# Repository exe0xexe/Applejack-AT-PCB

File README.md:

# PCB for converting AT layout keyboards to MX
### Powered by QMK/VIAL
## Layout

## Bill Of Materials 

### To build the keyboard, you will need the following materials
- 1x STM32F401CCU6 Blackpill
- Pins and sockets for the microcontrollers (blackpill needs 20 pin stripes)
- 98 1N4148 DO-35 diodes
- 22 Wire jumpers (you can use diode legs) 
- 4 82ohm resistors (optional)
- LED (optional)

## Completed build

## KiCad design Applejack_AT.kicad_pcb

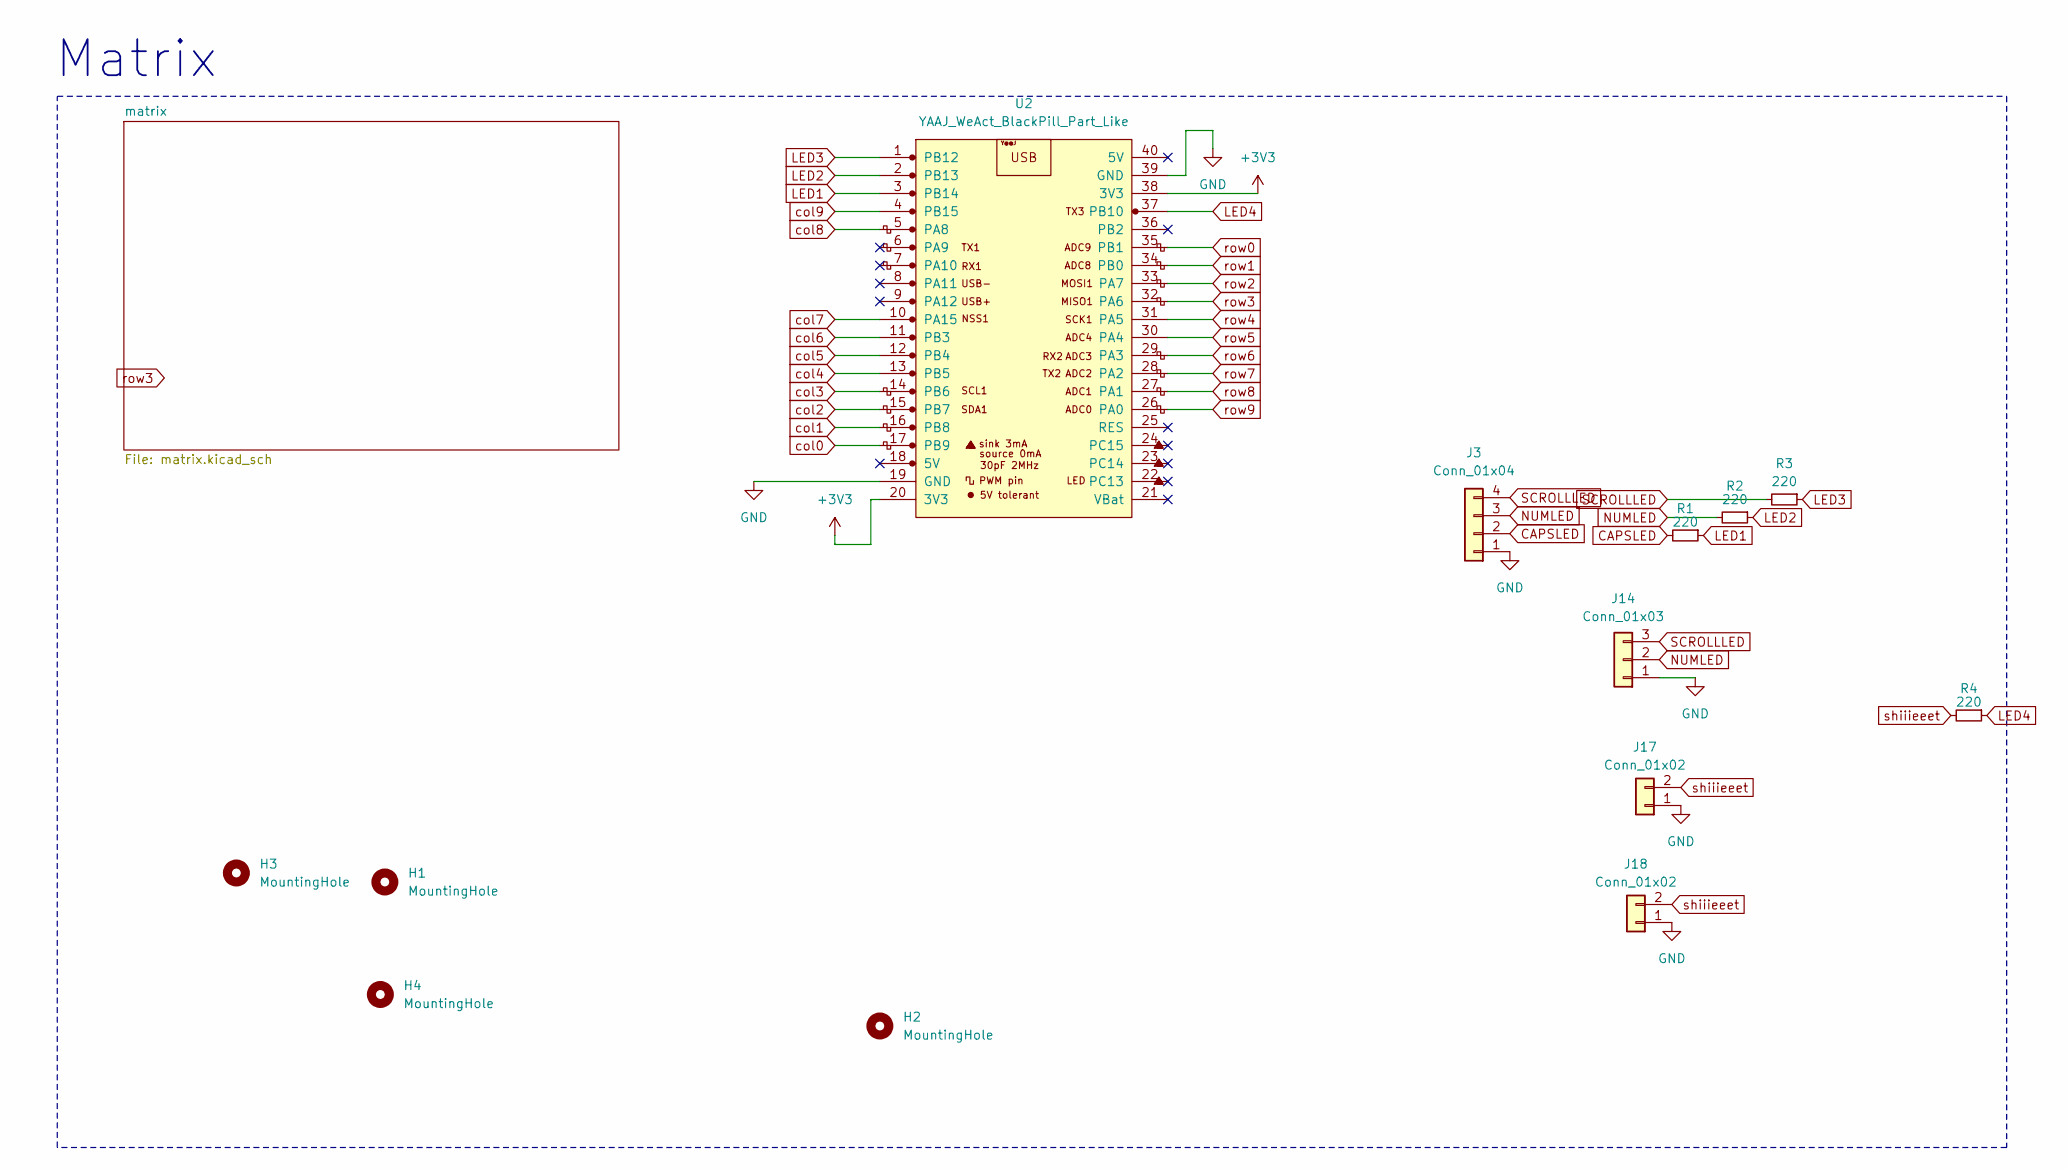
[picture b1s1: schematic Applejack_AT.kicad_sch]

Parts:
H1, H2, H3, H4: MountingHole; mousebites_2.5mm_4p
J3: Conn_01x04; PinHeader_1x04_P2.54mm_Horizontal
J14: Conn_01x03; 3pin
J17, J18: Conn_01x02; 2pin-GND
R1, R2, R3, R4: 220; R_Axial_DIN0207_L6.3mm_D2.5mm_P7.62mm_Horizontal_no_silkscr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
U2: YAAJ_WeAct_BlackPill_Part_Like; YAAJ_WeAct_BlackPill_2_twilight_sparkle_no_cut

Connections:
+3V3: U2.20 (3V3), U2.38 (3V3)
CAPSLED: J3.2, R1.2; also elsewhere on the board
GND: J3.1, J14.1, J17.1, J18.1, U2.19 (GND), U2.39 (GND); also elsewhere on the board
LED1: R1.1, U2.3 (PB14)
LED2: R2.1, U2.2 (PB13)
LED3: R3.1, U2.1 (PB12)
LED4: R4.1, U2.37 (PB10)
NUMLED: J3.3, J14.2, R2.2; also elsewhere on the board
SCROLLLED: J3.4, J14.3, R3.2; also elsewhere on the board
col0: U2.17 (PB9); also elsewhere on the board
col1: U2.16 (PB8); also elsewhere on the board
col2: U2.15 (PB7); also elsewhere on the board
col3: U2.14 (PB6); also elsewhere on the board
col4: U2.13 (PB5); also elsewhere on the board
col5: U2.12 (PB4); also elsewhere on the board
col6: U2.11 (PB3); also elsewhere on the board
col7: U2.10 (PA15); also elsewhere on the board
col8: U2.5 (PA8); also elsewhere on the board
col9: U2.4 (PB15); also elsewhere on the board
row0: U2.35 (PB1); also elsewhere on the board
row1: U2.34 (PB0); also elsewhere on the board
row2: U2.33 (PA7); also elsewhere on the board
row3: U2.32 (PA6); also elsewhere on the board
row4: U2.31 (PA5); also elsewhere on the board
row5: U2.30 (PA4); also elsewhere on the board
row6: U2.29 (PA3); also elsewhere on the board
row7: U2.28 (PA2); also elsewhere on the board
row8: U2.27 (PA1); also elsewhere on the board
row9: U2.26 (PA0); also elsewhere on the board
shiiieeet: J17.2, J18.2, R4.2; also elsewhere on the board

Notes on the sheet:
Matrix

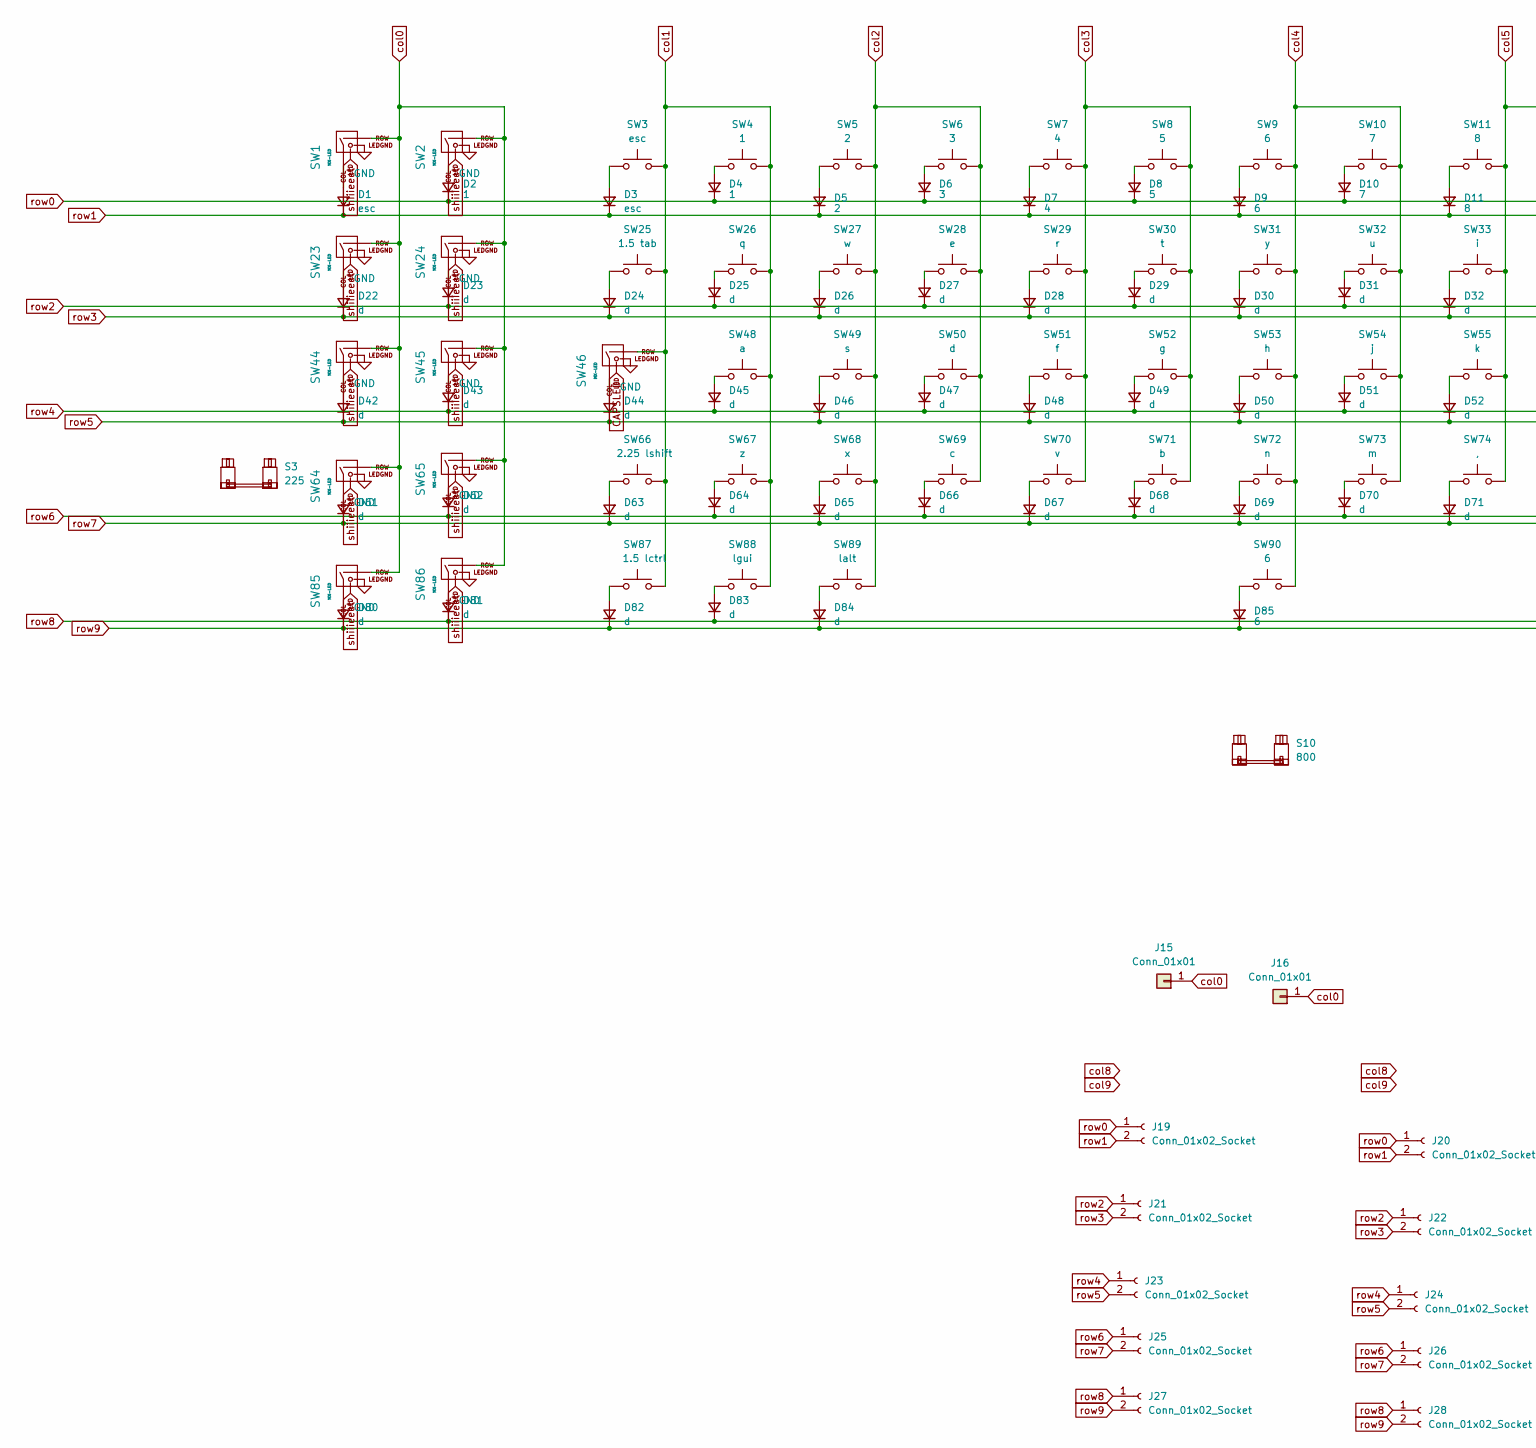
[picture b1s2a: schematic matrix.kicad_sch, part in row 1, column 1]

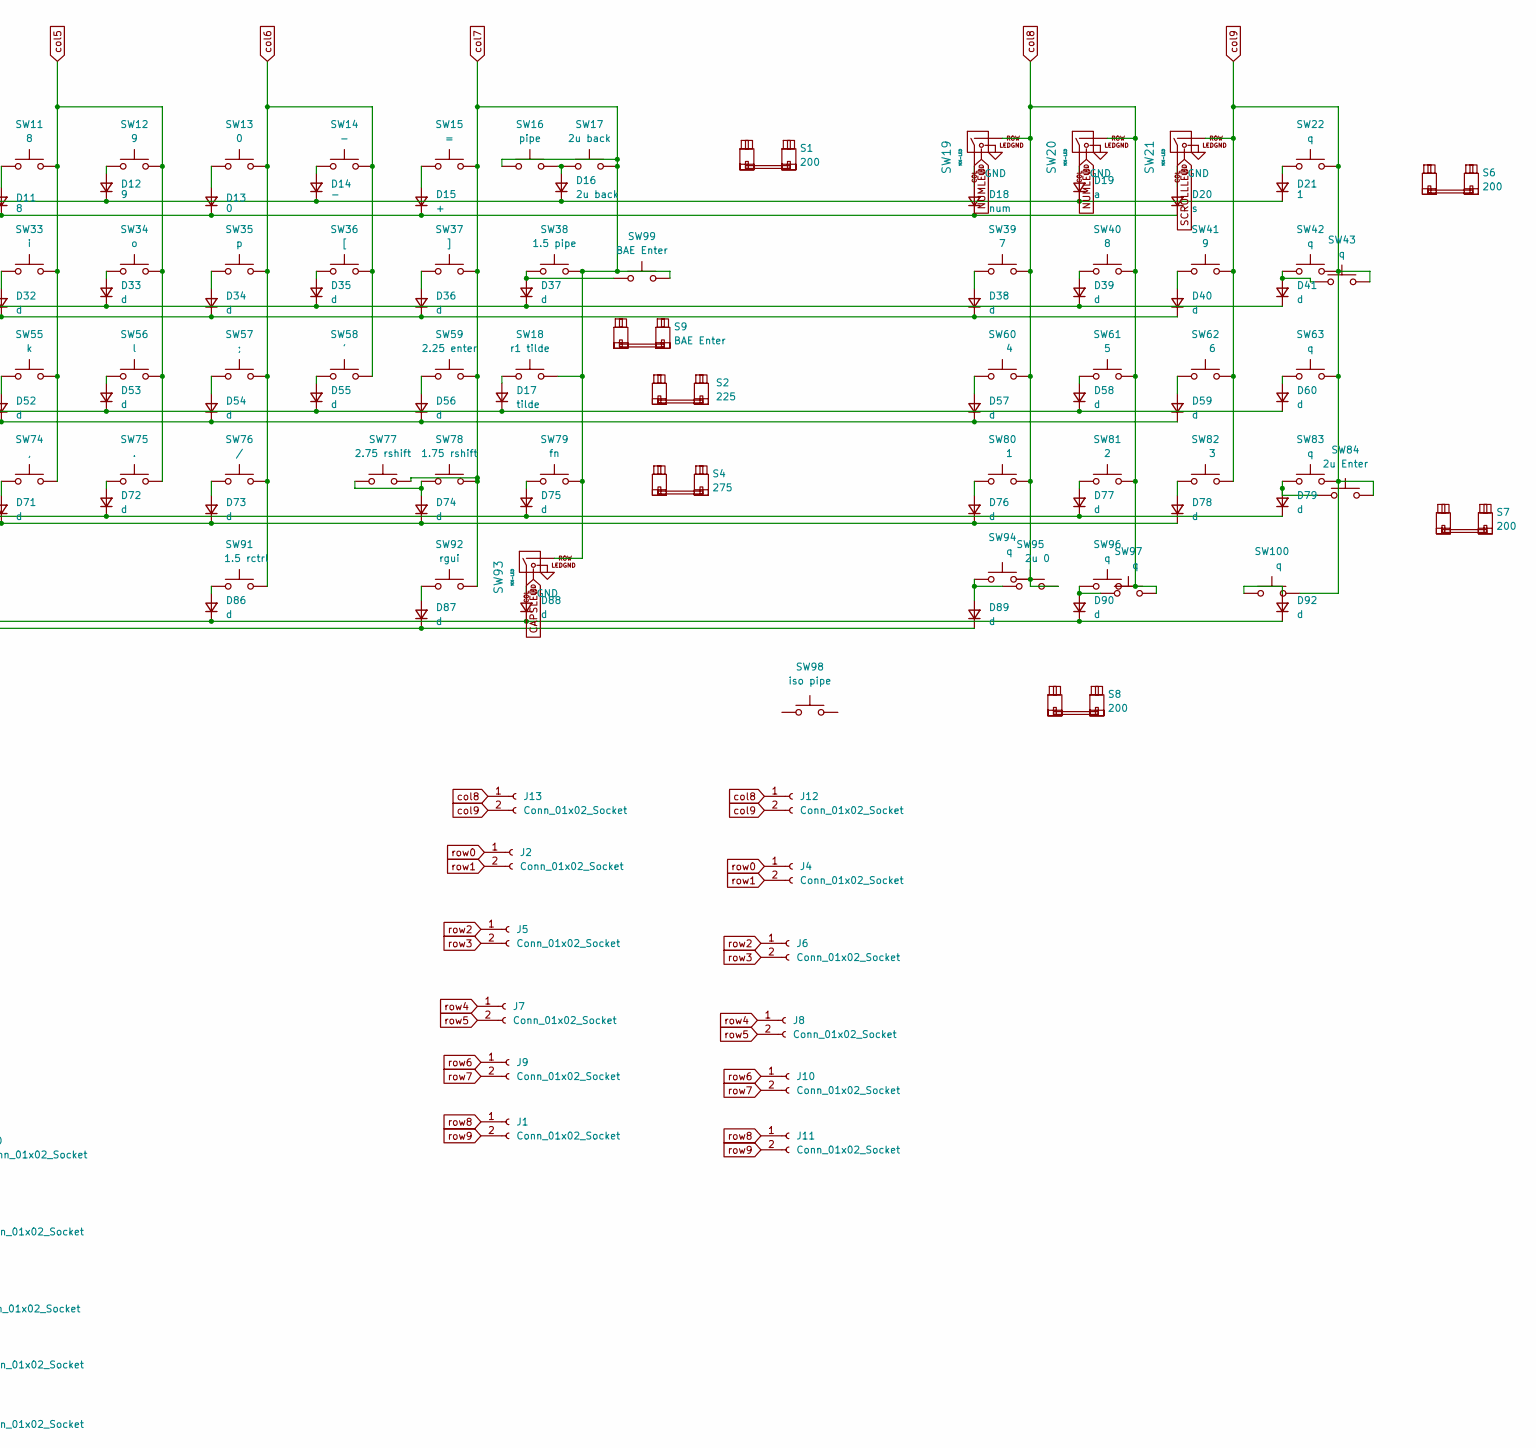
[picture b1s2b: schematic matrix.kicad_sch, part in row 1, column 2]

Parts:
D1, D3: esc; Diode_DO-35
D2, D4, D21: 1; Diode_DO-35
D5: 2; Diode_DO-35
D6: 3; Diode_DO-35
D7: 4; Diode_DO-35
D8: 5; Diode_DO-35
D9, D85: 6; Diode_DO-35
D10: 7; Diode_DO-35
D11: 8; Diode_DO-35
D12: 9; Diode_DO-35
D13: 0; Diode_DO-35
D14: -; Diode_DO-35
D15: +; Diode_DO-35
D16: 2u back; Diode_DO-35
D17: tilde; Diode_DO-35
D18: num; Diode_DO-35
D19: a; Diode_DO-35
D20: s; Diode_DO-35
D22, D23, D24, D25, D26, D27, D28, D29, D30, D31, D32, D33, D34, D35, D36, D37, D38, D39, D40, D41, D42, D43, D44, D45, D46, D47, D48, D49, D50, D51, D52, D53, D54, D55, D56, D57, D58, D59, D60, D61, D62, D63, D64, D65, D66, D67, D68, D69, D70, D71, D72, D73, D74, D75, D76, D77, D78, D79, D80, D81, D82, D83, D84, D86, D87, D88, D89, D90, D92: d; Diode_DO-35
J1, J2, J4, J5, J6, J7, J8, J9, J10, J11, J12, J13, J19, J20, J21, J22, J23, J24, J25, J26, J27, J28: Conn_01x02_Socket; 2pin
J15, J16: Conn_01x01; 1pin
S1, S6, S7, S8: 200; STAB_MX_2u
S2, S3: 225; STAB_MX_2.25u
S4: 275; STAB_MX_2.75u
S9: BAE Enter; STAB_MX_ISO
S10: 800; STAB_MX_10u
SW1, SW2, SW19, SW20, SW21, SW23, SW24, SW44, SW45, SW64, SW65, SW85, SW86, SW93: MX-LED; MX_1U_LED
SW3: esc; MX_1U
SW4, SW80: 1; MX_1U
SW5, SW81: 2; MX_1U
SW6, SW82: 3; MX_1U
SW7, SW60: 4; MX_1U
SW8, SW61: 5; MX_1U
SW9, SW62, SW90: 6; MX_1U
SW10, SW39: 7; MX_1U
SW11, SW40: 8; MX_1U
SW12, SW41: 9; MX_1U
SW13: 0; MX_1U
SW14: -; MX_1U
SW15: =; MX_1U
SW16: pipe; MX_1U
SW17: 2u back; MX_1U
SW18: r1 tilde; MX_1U
SW22, SW26, SW42, SW43, SW63, SW83, SW94, SW96, SW97, SW100: q; MX_1U
SW25: 1.5 tab; MX_1U
SW27: w; MX_1U
SW28: e; MX_1U
SW29: r; MX_1U
SW30: t; MX_1U
SW31: y; MX_1U
SW32: u; MX_1U
SW33: i; MX_1U
SW34: o; MX_1U
SW35: p; MX_1U
SW36: [; MX_1U
SW37: ]; MX_1U
SW38: 1.5 pipe; MX_1U
SW46: MX-LED; MX_CAPS
SW48: a; MX_1U
SW49: s; MX_1U
SW50: d; MX_1U
SW51: f; MX_1U
SW52: g; MX_1U
SW53: h; MX_1U
SW54: j; MX_1U
SW55: k; MX_1U
SW56: l; MX_1U
SW57: ;; MX_1U
SW58: '; MX_1U
SW59: 2.25 enter; MX_1U
SW66: 2.25 lshift; MX_1U
SW67: z; MX_1U
SW68: x; MX_1U
SW69: c; MX_1U
SW70: v; MX_1U
SW71: b; MX_1U
SW72: n; MX_1U
SW73: m; MX_1U
SW74: ,; MX_1U
SW75: .; MX_1U
SW76: /; MX_1U
SW77: 2.75 rshift; MX_1U
SW78: 1.75 rshift; MX_1U
SW79: fn; MX_1U
SW84: 2u Enter; MX_1U
SW87: 1.5 lctrl; MX_1U
SW88: lgui; MX_1U
SW89: lalt; MX_1U
SW91: 1.5 rctrl; MX_1U
SW92: rgui; MX_1U
SW95: 2u 0; MX_1U
SW98: iso pipe; MX_1U
SW99: BAE Enter; MX_1U

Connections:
CAPSLED: SW46.3 (LED), SW93.3 (LED); also elsewhere on the board
GND: SW1.4 (LEDGND), SW2.4 (LEDGND), SW19.4 (LEDGND), SW20.4 (LEDGND), SW21.4 (LEDGND), SW23.4 (LEDGND), SW24.4 (LEDGND), SW44.4 (LEDGND), SW45.4 (LEDGND), SW46.4 (LEDGND), SW64.4 (LEDGND), SW65.4 (LEDGND), SW85.4 (LEDGND), SW86.4 (LEDGND), SW93.4 (LEDGND); also elsewhere on the board
NUMLED: SW19.3 (LED), SW20.3 (LED); also elsewhere on the board
unnamed: D1.2 (A), SW1.1 (COL)
unnamed: D2.2 (A), SW2.1 (COL)
unnamed: D3.2 (A), SW3.1
unnamed: D4.2 (A), SW4.1
unnamed: D5.2 (A), SW5.1
unnamed: D6.2 (A), SW6.1
unnamed: D7.2 (A), SW7.1
unnamed: D8.2 (A), SW8.1
unnamed: D9.2 (A), SW9.1
unnamed: D10.2 (A), SW10.1
unnamed: D11.2 (A), SW11.1
unnamed: D12.2 (A), SW12.1
unnamed: D13.2 (A), SW13.1
unnamed: D14.2 (A), SW14.1
unnamed: D15.2 (A), SW15.1
unnamed: D16.2 (A), SW16.1, SW17.1
unnamed: D17.2 (A), SW18.1
unnamed: D18.2 (A), SW19.1 (COL)
unnamed: D19.2 (A), SW20.1 (COL)
unnamed: D20.2 (A), SW21.1 (COL)
unnamed: D21.2 (A), SW22.1
unnamed: D22.2 (A), SW23.1 (COL)
unnamed: D23.2 (A), SW24.1 (COL)
unnamed: D24.2 (A), SW25.1
unnamed: D25.2 (A), SW26.1
unnamed: D26.2 (A), SW27.1
unnamed: D27.2 (A), SW28.1
unnamed: D28.2 (A), SW29.1
unnamed: D29.2 (A), SW30.1
unnamed: D30.2 (A), SW31.1
unnamed: D31.2 (A), SW32.1
unnamed: D32.2 (A), SW33.1
unnamed: D33.2 (A), SW34.1
unnamed: D34.2 (A), SW35.1
unnamed: D35.2 (A), SW36.1
unnamed: D36.2 (A), SW37.1
unnamed: D37.2 (A), SW38.1, SW99.1
unnamed: D38.2 (A), SW39.1
unnamed: D39.2 (A), SW40.1
unnamed: D40.2 (A), SW41.1
unnamed: D41.2 (A), SW42.1, SW43.1
unnamed: D42.2 (A), SW44.1 (COL)
unnamed: D43.2 (A), SW45.1 (COL)
unnamed: D44.2 (A), SW46.1 (COL)
unnamed: D45.2 (A), SW48.1
unnamed: D46.2 (A), SW49.1
unnamed: D47.2 (A), SW50.1
unnamed: D48.2 (A), SW51.1
unnamed: D49.2 (A), SW52.1
unnamed: D50.2 (A), SW53.1
unnamed: D51.2 (A), SW54.1
unnamed: D52.2 (A), SW55.1
unnamed: D53.2 (A), SW56.1
unnamed: D54.2 (A), SW57.1
unnamed: D55.2 (A), SW58.1
unnamed: D56.2 (A), SW59.1
unnamed: D57.2 (A), SW60.1
unnamed: D58.2 (A), SW61.1
unnamed: D59.2 (A), SW62.1
unnamed: D60.2 (A), SW63.1
unnamed: D61.2 (A), SW64.1 (COL)
unnamed: D62.2 (A), SW65.1 (COL)
unnamed: D63.2 (A), SW66.1
unnamed: D64.2 (A), SW67.1
unnamed: D65.2 (A), SW68.1
unnamed: D66.2 (A), SW69.1
unnamed: D67.2 (A), SW70.1
unnamed: D68.2 (A), SW71.1
unnamed: D69.2 (A), SW72.1
unnamed: D70.2 (A), SW73.1
unnamed: D71.2 (A), SW74.1
unnamed: D72.2 (A), SW75.1
unnamed: D73.2 (A), SW76.1
unnamed: D74.2 (A), SW77.1, SW78.1
unnamed: D75.2 (A), SW79.1
unnamed: D76.2 (A), SW80.1
unnamed: D77.2 (A), SW81.1
unnamed: D78.2 (A), SW82.1
unnamed: D79.2 (A), SW83.1, SW84.1
unnamed: D80.2 (A), SW85.1 (COL)
unnamed: D81.2 (A), SW86.1 (COL)
unnamed: D82.2 (A), SW87.1
unnamed: D83.2 (A), SW88.1
unnamed: D84.2 (A), SW89.1
unnamed: D85.2 (A), SW90.1
unnamed: D86.2 (A), SW91.1
unnamed: D87.2 (A), SW92.1
unnamed: D88.2 (A), SW93.1 (COL)
unnamed: D89.2 (A), SW94.1, SW95.1
unnamed: D90.2 (A), SW96.1, SW97.1
unnamed: D92.2 (A), SW100.1
SCROLLLED: SW21.3 (LED); also elsewhere on the board
col0: J15.1, J16.1, SW1.2 (ROW), SW2.2 (ROW), SW23.2 (ROW), SW24.2 (ROW), SW44.2 (ROW), SW45.2 (ROW), SW64.2 (ROW), SW65.2 (ROW), SW85.2 (ROW), SW86.2 (ROW); also elsewhere on the board
col1: SW3.2, SW4.2, SW25.2, SW26.2, SW46.2 (ROW), SW48.2, SW66.2, SW67.2, SW87.2, SW88.2; also elsewhere on the board
col2: SW5.2, SW6.2, SW27.2, SW28.2, SW49.2, SW50.2, SW68.2, SW69.2, SW89.2; also elsewhere on the board
col3: SW7.2, SW8.2, SW29.2, SW30.2, SW51.2, SW52.2, SW70.2, SW71.2; also elsewhere on the board
col4: SW9.2, SW10.2, SW31.2, SW32.2, SW53.2, SW54.2, SW72.2, SW73.2, SW90.2; also elsewhere on the board
col5: SW11.2, SW12.2, SW33.2, SW34.2, SW55.2, SW56.2, SW74.2, SW75.2; also elsewhere on the board
col6: SW13.2, SW14.2, SW35.2, SW36.2, SW57.2, SW58.2, SW76.2, SW91.2; also elsewhere on the board
col7: SW15.2, SW16.2, SW17.2, SW18.2, SW37.2, SW38.2, SW59.2, SW77.2, SW78.2, SW79.2, SW92.2, SW93.2 (ROW), SW99.2; also elsewhere on the board
col8: J12.1, J13.1, SW19.2 (ROW), SW20.2 (ROW), SW39.2, SW40.2, SW60.2, SW61.2, SW80.2, SW81.2, SW94.2, SW95.2, SW96.2, SW97.2; also elsewhere on the board
col9: J12.2, J13.2, SW21.2 (ROW), SW22.2, SW41.2, SW42.2, SW43.2, SW62.2, SW63.2, SW82.2, SW83.2, SW84.2, SW100.2; also elsewhere on the board
row0: D2.1 (K), D4.1 (K), D6.1 (K), D8.1 (K), D10.1 (K), D12.1 (K), D14.1 (K), D16.1 (K), D19.1 (K), D21.1 (K), J2.1, J4.1, J19.1, J20.1; also elsewhere on the board
row1: D1.1 (K), D3.1 (K), D5.1 (K), D7.1 (K), D9.1 (K), D11.1 (K), D13.1 (K), D15.1 (K), D18.1 (K), D20.1 (K), J2.2, J4.2, J19.2, J20.2; also elsewhere on the board
row2: D23.1 (K), D25.1 (K), D27.1 (K), D29.1 (K), D31.1 (K), D33.1 (K), D35.1 (K), D37.1 (K), D39.1 (K), D41.1 (K), J5.1, J6.1, J21.1, J22.1; also elsewhere on the board
row3: D22.1 (K), D24.1 (K), D26.1 (K), D28.1 (K), D30.1 (K), D32.1 (K), D34.1 (K), D36.1 (K), D38.1 (K), D40.1 (K), J5.2, J6.2, J21.2, J22.2; also elsewhere on the board
row4: D17.1 (K), D43.1 (K), D45.1 (K), D47.1 (K), D49.1 (K), D51.1 (K), D53.1 (K), D55.1 (K), D58.1 (K), D60.1 (K), J7.1, J8.1, J23.1, J24.1; also elsewhere on the board
row5: D42.1 (K), D44.1 (K), D46.1 (K), D48.1 (K), D50.1 (K), D52.1 (K), D54.1 (K), D56.1 (K), D57.1 (K), D59.1 (K), J7.2, J8.2, J23.2, J24.2; also elsewhere on the board
row6: D62.1 (K), D64.1 (K), D66.1 (K), D68.1 (K), D70.1 (K), D72.1 (K), D75.1 (K), D77.1 (K), D79.1 (K), J9.1, J10.1, J25.1, J26.1; also elsewhere on the board
row7: D61.1 (K), D63.1 (K), D65.1 (K), D67.1 (K), D69.1 (K), D71.1 (K), D73.1 (K), D74.1 (K), D76.1 (K), D78.1 (K), J9.2, J10.2, J25.2, J26.2; also elsewhere on the board
row8: D81.1 (K), D83.1 (K), D86.1 (K), D88.1 (K), D90.1 (K), D92.1 (K), J1.1, J11.1, J27.1, J28.1; also elsewhere on the board
row9: D80.1 (K), D82.1 (K), D84.1 (K), D85.1 (K), D87.1 (K), D89.1 (K), J1.2, J11.2, J27.2, J28.2; also elsewhere on the board
shiiieeet: SW1.3 (LED), SW2.3 (LED), SW23.3 (LED), SW24.3 (LED), SW44.3 (LED), SW45.3 (LED), SW64.3 (LED), SW65.3 (LED), SW85.3 (LED), SW86.3 (LED); also elsewhere on the board

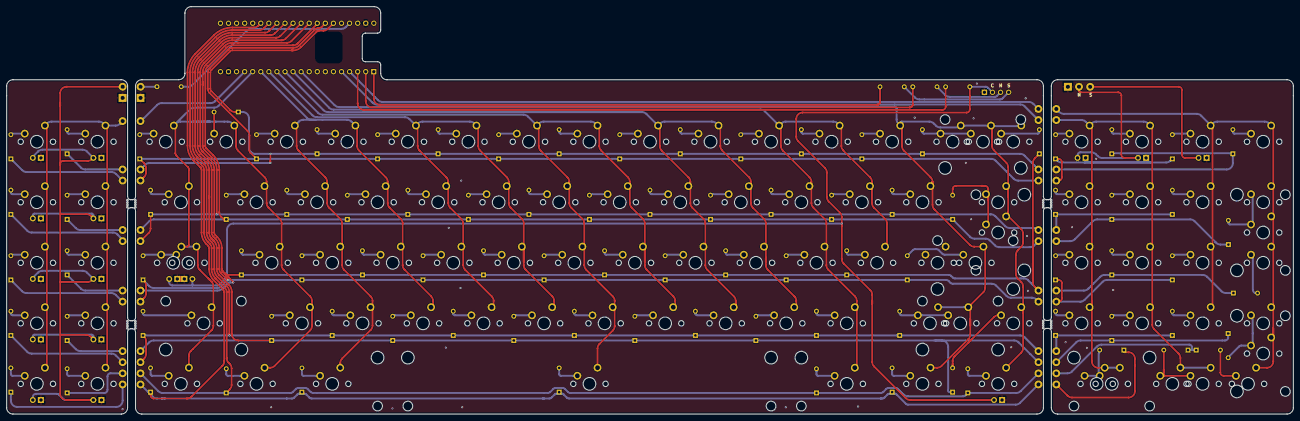
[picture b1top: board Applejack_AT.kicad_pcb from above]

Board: 2 copper layers, 404.9 x 128.2 mm, 236 parts (1 on the bottom side), 121 nets.
